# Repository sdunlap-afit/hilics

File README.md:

<div>
  
</div>
<br clear="all" />
<br>

<div align="center">

</div>

# HILICS - Hardware-in-the-loop industrial control system training platform

The Center for Cyberspace Research (CCR) has conducted extensive research in Industrial Control System (ICS) security. ICS architectures utilize a variety of proprietary hardware and software configurations to control and monitor industrial processes and safety systems. Defenders must be familiar with the functionality, requirements and limitations of control systems in order to successfully defend them from cyber-attacks. Hands-on training and experience is crucial for defenders who must be able to interact safely with a given control system. Without this experience, defenders could mistakenly take actions that cause more harm to the system than a basic cyber-attack.  

Given the physical nature of ICS architectures, training platforms can be difficult and costly to develop. To address this, the CCR has developed HILICS - a unique hardware-in-the-loop ICS platform designed to support training, education and research. HILICS utilizes a MicroLogix 1100 Programmable Logic Controller (PLC) to introduce students to PLC operating basics and the associated programming languages. This PLC is a low-cost commercial product that provides a representative set of features to give students exposure to control system functionality. The HILICS platform is a custom hardware-in-the-loop system that enables trainers to incorporate multiple physical process simulations and expose students to a range of control system applications. The platform is designed to be flexible and scalable, allowing for varying class sizes and supporting various control system applications.  

# How it works

HILICS is a hardware-in-the-loop training system. A Raspberry Pi provides simulations of physical processes such as fluid tanks or garage doors. Each simulation is made up of sensors, actuators and physical components such as pipes or tanks. **The Raspberry Pi does not have any network connection to the PLC.**

We will use the tank simulation as an example.

## Sensors

The Raspberry Pi simulation determines the current state of the process and calculates the values of the simulated sensors. The sensor values are sent to the PLC via the interface PCB. The PLC receives these values as voltages using it's digital and analog inputs. The PLC's ladder logic program determines how the PLC responds to the sensor values.

For the tank, there are two analog sensors and three digital sensors.

* Analog Sensors:
	* Inflow differential pressure transmitter.
	* Fluid level differential pressure transmitter.
* Digital Sensors:
	* Low level float
	* High level float
	* High-High level float
* Other:
	* This simulation was designed to work without the presence of an HMI. Typically, an HMI would be used to select set points for the process.
	* The Inflow SP button panel uses two of the PLC's digital inputs to send the desired inflow rate to the PLC.
	* The Level SP button panel uses two of the PLC's digital inputs to send the desired fluid level of the tank to the PLC.

## Actuators

The PLC reads the values of the sensors, compares them to the desired values and then adjusts it's outputs (as voltages) to control the actuators. The Raspberry Pi receives these values via the interface PCB and adjusts the simulation appropriately. 

For the tank, there are two analog actuators.

* Pump - the speed of the pump is used to calculate the current inflow rate into the tank.
* Valve - the position of the valve is used to calculate the outflow rate draining from the tank.

While the tank only has analog actuators, an example of a digital actuator is an indicator light controlled by the PLC's digital outputs.

Find further details about this simulation [here.](../labs/L3_Tank_Control.md)

# What's Included

## Documentation

The [docs](./docs) folder contains various documents including a bill-of-materials, hardware assembly and computer setup instructions.

## Source code

This repository contains all of the Python [source code](./src) you need to get started. The [apps](./src/apps) folder contains the following Applications:

* [IO_Test.py](./src/apps/IO_Test.py) - Basic app to test the functionality of the HILICS kit.
* [Door.py](./src/apps/Door.py) - Garage door simulation.
* [Fluid_Tank.py](./src/apps/Fluid_Tank.py) - Fluid tank with two control loops.
* [Blank_App.py](./src/apps/Blank_App.py) - A template to help you get started writing your own app.
* [Test_App.py](./src/apps/Test_App.py) - An app you can enable and edit to test your display elements during development.

## Hardware

The [hardware](./hardware) folder contains the design files and stl files you need to 3D print the frame for HILICS.

The [eagle](./hardware/eagle) folder contains all of the PCB design files and BOM.

## Labs

HILICS was designed for use in cyber security education, but the labs released here only cover basic PLC operations. Future labs may cover cyber concepts. 

The [labs](./labs) folder contains three basic labs to get started.

* [Lab 1](./labs/L1_Setup.md) - Get connected to your PLC and start programming in ladder logic.
* [Lab 2](./labs/L2_Door_Control.md) - Write a ladder logic program to control a garage door simulation.
* [Lab 3](./labs/L3_Tank_Control.md) - Learn the basics of PID control and PID tuning.

# Getting Started

## [Read the docs](./docs/README.md)

## [Try the labs](./labs/README.md)

## Contribute

This repository is not currently maintained and we will not be accepting any pull requests. If we develop any additional capabilities, we will release them here. If enough interest is shown, we might begin actively maintaining the repository. 

If you would like to contribute, look at the existing forks, or feel free to start your own.

# Disclaimer

Note that the views expressed in this project are those of
the authors and do not reflect the official policy or position of
the U.S. Air Force, U.S. Department of Defense or the U.S.
Government.

Approved for public release, 24 Sep 2019, Case #88ABW-2019-4607.

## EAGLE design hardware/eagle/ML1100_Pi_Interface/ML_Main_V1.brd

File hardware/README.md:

<div>
  
</div>
<br clear="all" />
<br>

# Custom Hardware

## [Interface PCBs](./eagle/ML1100_Pi_Interface)

For each HILICS kit, you will need one each of the five [Interface PCBs](./eagle/ML1100_Pi_Interface). The bill of materials is in the folder with the PCBs. The BOM is for Digikey but provides specifications if you want to source components from a different supplier.

**You will also need 40-pin male headers for the Raspberry Pi ribbon cable to connect to the main PCB. These are cheaper on Amazon.**

If you plan to solder these by hand, make sure you are competent with surface mount soldering techniques. It may also be helpful to modify the main PCB design to use resistor arrays instead of individual resistors. Similar modifications can help reduce the amount of soldering required.

## [3D printing](./cad/stl_files)

The frame was designed in sections so that the largest part (135mm x 210mm) would still fit on a smaller 3D printer. 
We printed all of our components using black PLA without any supports. 
The amount of time and filament it will take depends heavily on your 3D printer settings.

 Our settings:

* 0.4mm layer height (0.2mm first layer height)
* 0.6mm nozzle
* 2 perimeters
* 3 bottom layers
* 3 top layers
* 20% infill

You will need to 3D print the following stl files (quantities listed):

* 1x - PLC Frame - 1x_HILICS_PLC_Frm.stl
* 2x - Raspberry PI Frame - 2x_HILICS_Pi_Frm.stl
* 2x - PCB legs - 2x_PCB_Leg.stl
* 3x - Extension Blocks - 3x_HILICS_ExtBlck.stl
* 1x - Choice of power box:
	* Multi-color: HILICS_Power_Color_* are individual stl files for multi-extruder/multi-color printers.
	* Single-color: HILICS_Power_single_ext.stl is for single extruder/color printers.

If you need to make modifications to the design, the Fusion 360 design files are [here.](./cad/Fusion360)

## [Nameplates](./cad/Nameplates)

You may also want to print [nameplates](./cad/Nameplates) for the front of your Pelican cases to uniquely identify each HILICS kit. We printed ours in white PLA

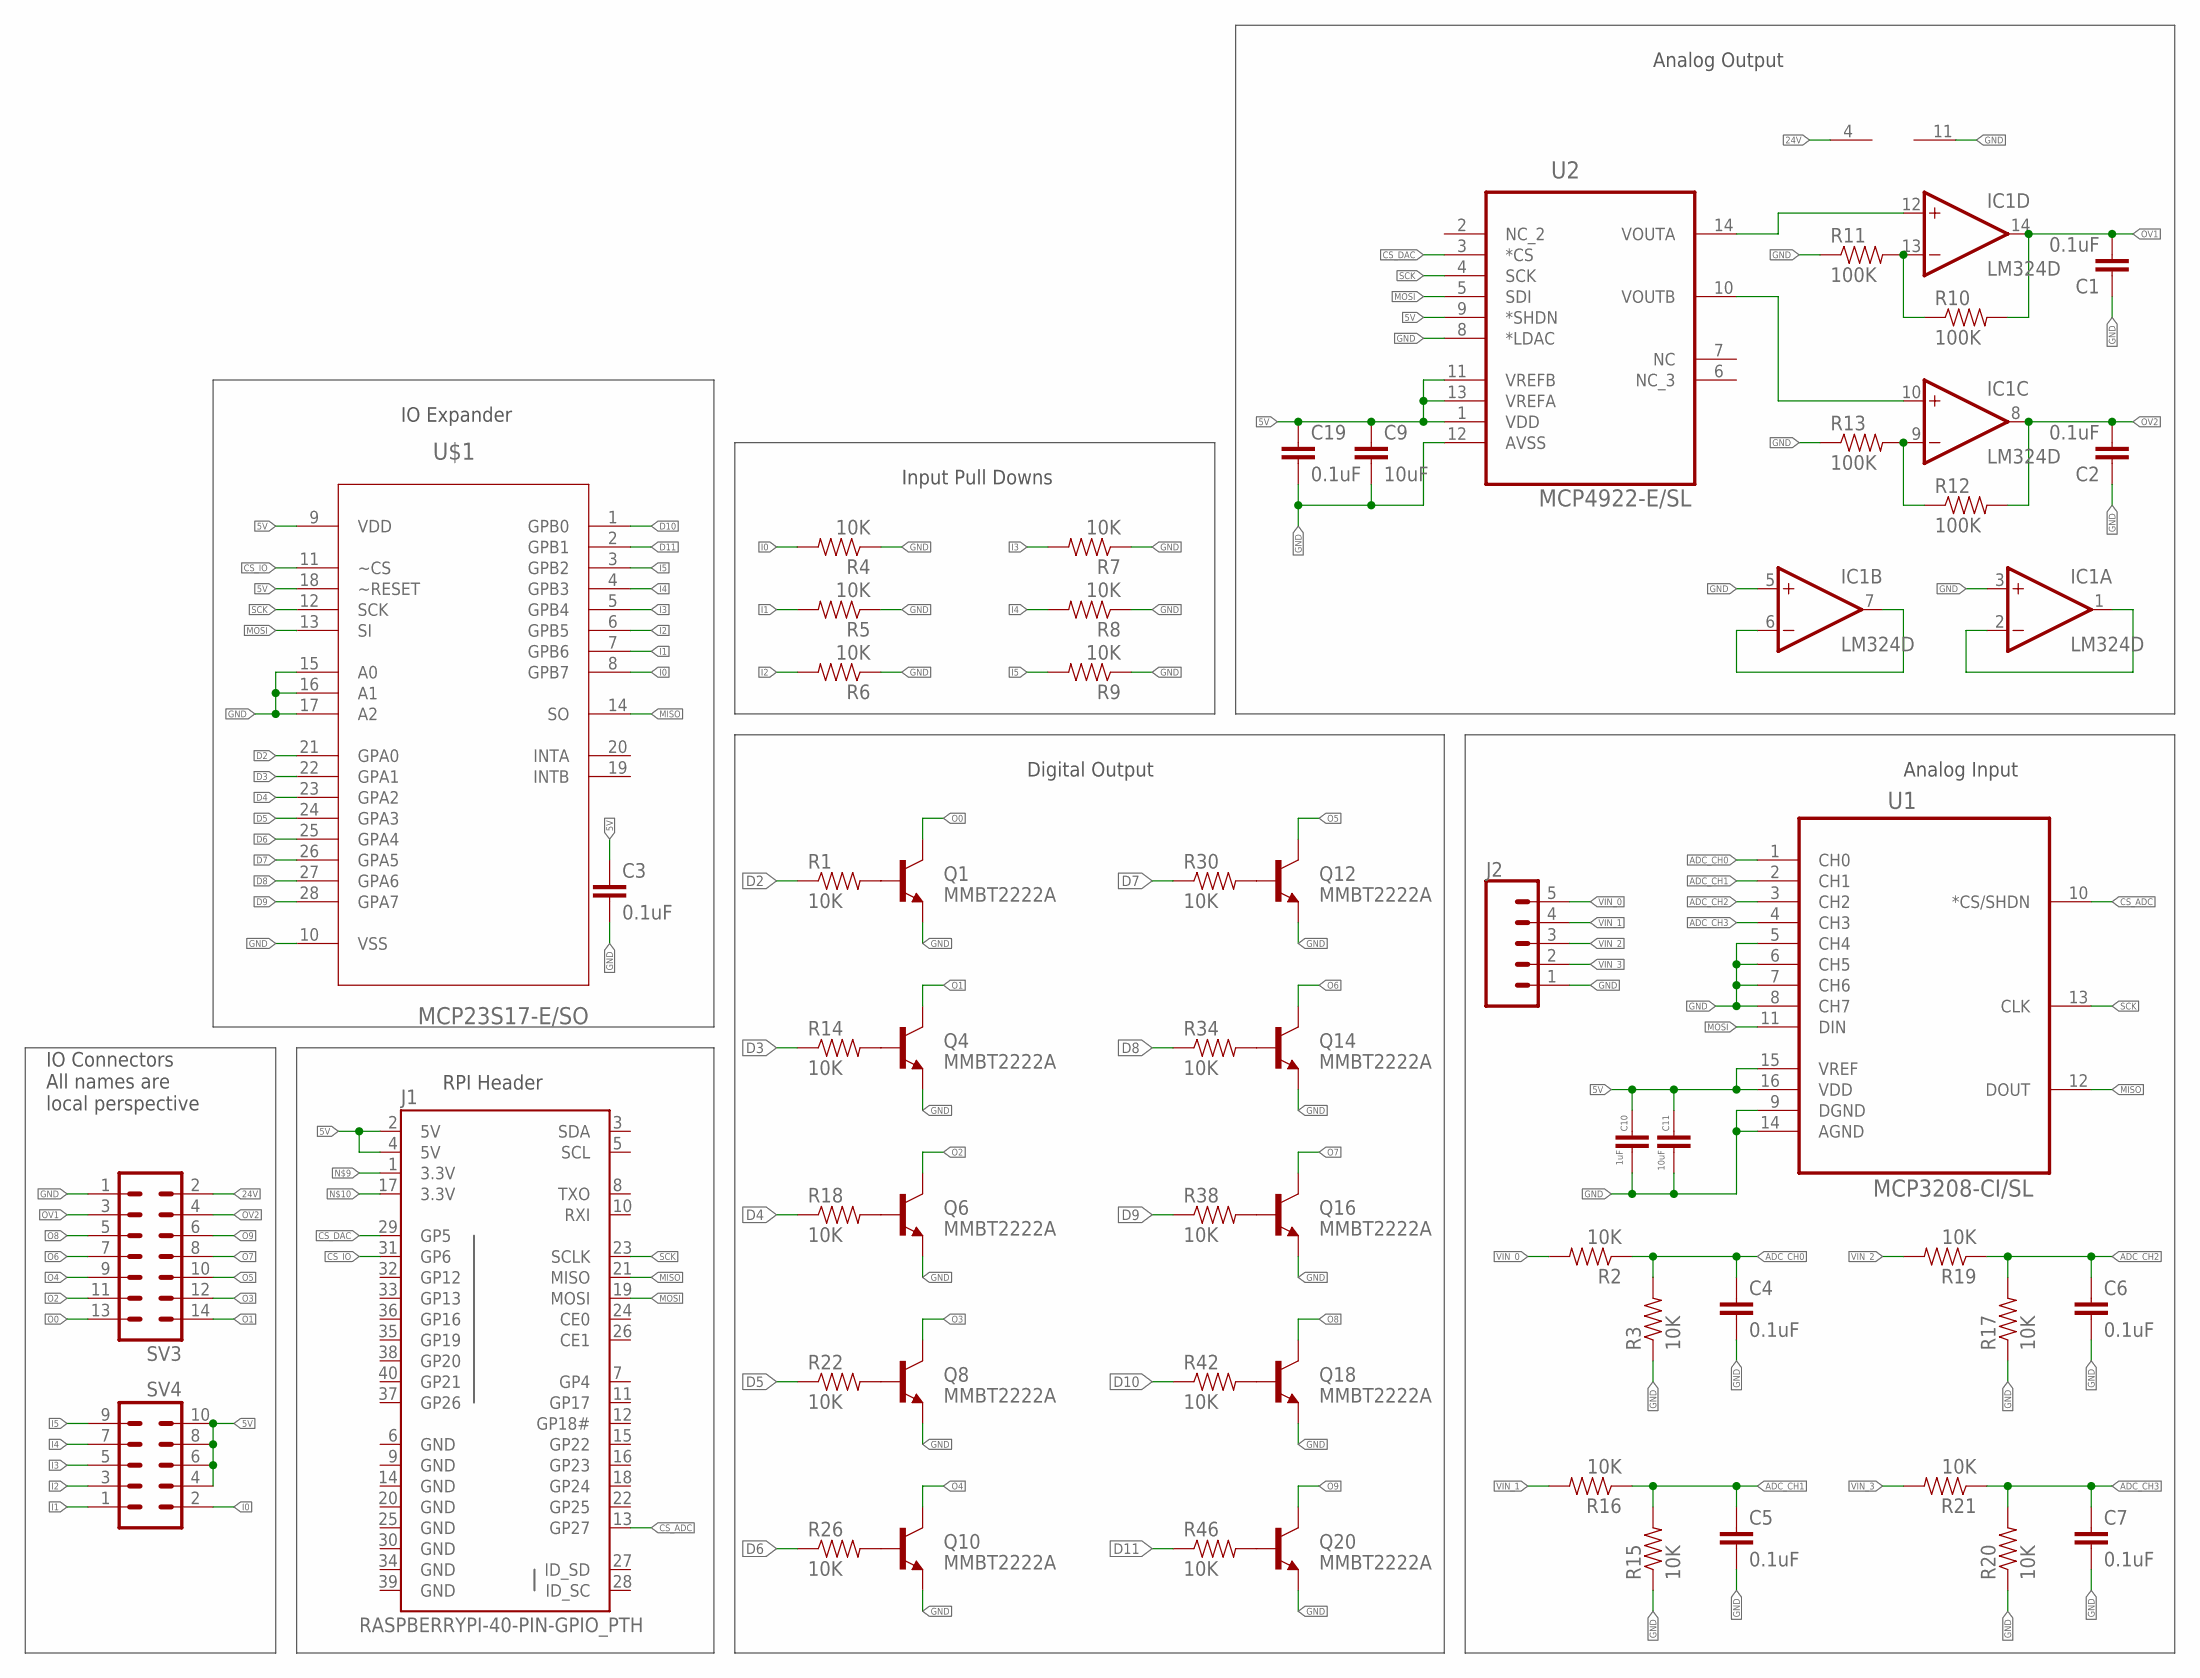
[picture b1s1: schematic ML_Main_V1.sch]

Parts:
C1, C2, C3, C4, C5, C6, C7, C19: 0.1uF; 0603-CAP
C9, C11: 10uF; 0603-CAP
C10: 1uF; 0603-CAP
IC1: LM324D; SO14
J1: RASPBERRYPI-40-PIN-GPIO_PTH; 2X20_SHROUDED
J2: CONN_05SCREW; SCREWTERMINAL-3.5MM-5
Q1, Q4, Q6, Q8, Q10, Q12, Q14, Q16, Q18, Q20: MMBT2222A; SOT23-3
R1, R2, R3, R4, R5, R6, R7, R8, R9, R14, R15, R16, R17, R18, R19, R20, R21, R22, R26, R30, R34, R38, R42, R46: 10K; 0603-RES
R10, R11, R12, R13: 100K; 0603-RES
SV3: MA07-2W
SV4: MA05-2
U1: MCP3208-CI/SL; SOIC127P600X175-16N
U2: MCP4922-E/SL; SOIC127P600X175-14N
U$1: MCP23S17-E/SO; SOIC127P030X265-28N

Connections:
5V: C3.1, C9.1, C10.1, C11.1, C19.1, J1.2 (5V), J1.4 (5V), SV4.4, SV4.6, SV4.8, SV4.10, U1.15 (VREF), U1.16 (VDD), U2.1 (VDD), U2.9 (*SHDN), U2.11 (VREFB), U2.13 (VREFA), U$1.9 (VDD), U$1.18 (~RESET)
24V: IC1.4 (V+), SV3.2
ADC_CH0: C4.1, R2.1, R3.2, U1.1 (CH0)
ADC_CH1: C5.1, R15.2, R16.1, U1.2 (CH1)
ADC_CH2: C6.1, R17.2, R19.1, U1.3 (CH2)
ADC_CH3: C7.1, R20.2, R21.1, U1.4 (CH3)
CS_ADC: J1.13 (GP27), U1.10 (*CS/SHDN)
CS_DAC: J1.29 (GP5), U2.3 (*CS)
CS_IO: J1.31 (GP6), U$1.11 (~CS)
D2: R1.1, U$1.21 (GPA0)
D3: R14.1, U$1.22 (GPA1)
D4: R18.1, U$1.23 (GPA2)
D5: R22.1, U$1.24 (GPA3)
D6: R26.1, U$1.25 (GPA4)
D7: R30.1, U$1.26 (GPA5)
D8: R34.1, U$1.27 (GPA6)
D9: R38.1, U$1.28 (GPA7)
D10: R42.1, U$1.1 (GPB0)
D11: R46.1, U$1.2 (GPB1)
GND: C1.1, C2.1, C3.2, C4.2, C5.2, C6.2, C7.2, C9.2, C10.2, C11.2, C19.2, IC1.3 (+IN), IC1.5 (+IN), IC1.11 (V-), J1.6 (GND), J1.9 (GND), J1.14 (GND), J1.20 (GND), J1.25 (GND), J1.30 (GND), J1.34 (GND), J1.39 (GND), J2.1, Q1.2 (E), Q4.2 (E), Q6.2 (E), Q8.2 (E), Q10.2 (E), Q12.2 (E), Q14.2 (E), Q16.2 (E), Q18.2 (E), Q20.2 (E), R3.1, R4.1, R5.1, R6.1, R7.1, R8.1, R9.1, R11.1, R13.1, R15.1, R17.1, R20.1, SV3.1, U1.5 (CH4), U1.6 (CH5), U1.7 (CH6), U1.8 (CH7), U1.9 (DGND), U1.14 (AGND), U2.8 (*LDAC), U2.12 (AVSS), U$1.10 (VSS), U$1.15 (A0), U$1.16 (A1), U$1.17 (A2)
I0: R4.2, SV4.2, U$1.8 (GPB7)
I1: R5.2, SV4.1, U$1.7 (GPB6)
I2: R6.2, SV4.3, U$1.6 (GPB5)
I3: R7.2, SV4.5, U$1.5 (GPB4)
I4: R8.2, SV4.7, U$1.4 (GPB3)
I5: R9.2, SV4.9, U$1.3 (GPB2)
MISO: J1.21 (MISO), U1.12 (DOUT), U$1.14 (SO)
MOSI: J1.19 (MOSI), U1.11 (DIN), U2.5 (SDI), U$1.13 (SI)
unnamed: IC1.13 (-IN), R10.1, R11.2
unnamed: Q1.1 (B), R1.2
unnamed: IC1.10 (+IN), U2.10 (VOUTB)
unnamed: IC1.12 (+IN), U2.14 (VOUTA)
unnamed: IC1.9 (-IN), R12.1, R13.2
unnamed: IC1.1 (OUT), IC1.2 (-IN)
unnamed: IC1.6 (-IN), IC1.7 (OUT)
unnamed: Q4.1 (B), R14.2
unnamed: Q6.1 (B), R18.2
unnamed: Q8.1 (B), R22.2
unnamed: Q10.1 (B), R26.2
unnamed: Q12.1 (B), R30.2
unnamed: Q14.1 (B), R34.2
unnamed: Q16.1 (B), R38.2
unnamed: Q18.1 (B), R42.2
unnamed: Q20.1 (B), R46.2
O0: Q1.3 (C), SV3.13
O1: Q4.3 (C), SV3.14
O2: Q6.3 (C), SV3.11
O3: Q8.3 (C), SV3.12
O4: Q10.3 (C), SV3.9
O5: Q12.3 (C), SV3.10
O6: Q14.3 (C), SV3.7
O7: Q16.3 (C), SV3.8
O8: Q18.3 (C), SV3.5
O9: Q20.3 (C), SV3.6
OV1: C1.2, IC1.14 (OUT), R10.2, SV3.3
OV2: C2.2, IC1.8 (OUT), R12.2, SV3.4
SCK: J1.23 (SCLK), U1.13 (CLK), U2.4 (SCK), U$1.12 (SCK)
VIN_0: J2.5, R2.2
VIN_1: J2.4, R16.2
VIN_2: J2.3, R19.2
VIN_3: J2.2, R21.2

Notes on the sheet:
IO Connectors All names are local perspective
Digital Output
Input Pull Downs
Analog Output
RPI Header
IO Expander
Analog Input

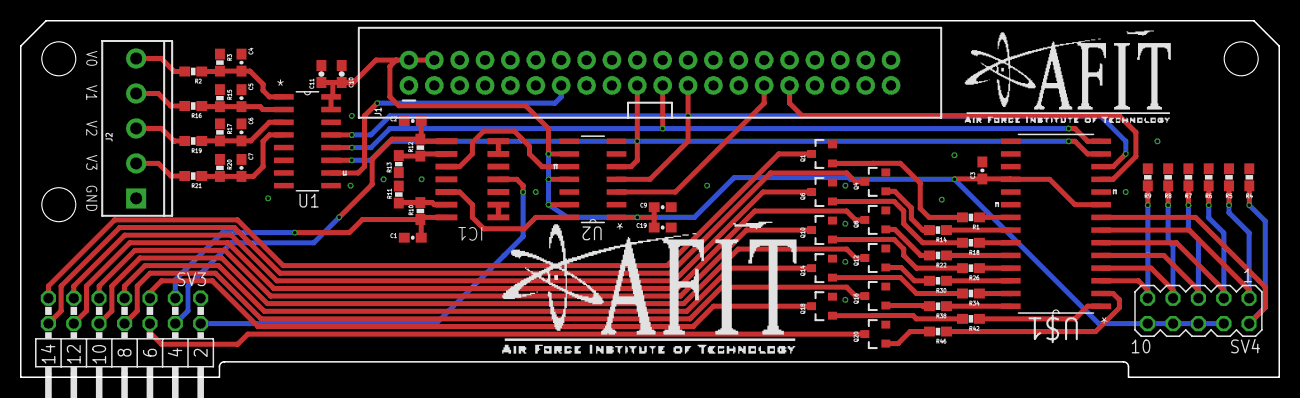
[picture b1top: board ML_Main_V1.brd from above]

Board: 2 copper layers, 126.0 x 35.7 mm, 57 parts (0 on the bottom side), 61 nets.

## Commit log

2021-01-05 Updated to match newest rpi OS version
2021-03-29 Bump pygments from 2.3.1 to 2.7.4 in /hardware/cad/Nameplates
    Bumps [pygments](https://github.com/pygments/pygments) from 2.3.1 to 2.7.4.
    - [Release notes](https://github.com/pygments/pygments/releases)
    - [Changelog](https://github.com/pygments/pygments/blob/master/CHANGES)
    - [Commits](https://github.com/pygments/pygments/compare/2.3.1...2.7.4)
2021-06-17 Fixed bug that broke pump and valve in tank sim
2021-07-06 Changed colors to match github dark mode
2021-07-06 Added background for github dark mode
2021-07-15 Fixed a threading bug
2021-11-09 Added standard python gitignore
2021-11-09 Template setup for blank sim
2021-11-19 Added base ServerRoom app
2021-11-19 ignore vscode folder
2021-11-19 Comm class for network sensors/actuators
2021-12-17 Refactored SimIO and start linking up sensors/actuators
2022-01-07 Added graphic for server rack
2022-01-14 Added servers and zone classes with basic numbers
2022-01-21 Bump ipython from 7.2.0 to 7.16.3 in /hardware/cad/Nameplates
    Bumps [ipython](https://github.com/ipython/ipython) from 7.2.0 to 7.16.3.
    - [Release notes](https://github.com/ipython/ipython/releases)
    - [Commits](https://github.com/ipython/ipython/compare/7.2.0...7.16.3)
    ---
    updated-dependencies:
    - dependency-name: ipython
2022-01-21 Basic simulation working
2023-05-03 Updated install scripts for tinker board and vnc

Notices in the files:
parts and their libraries:
SparkFun-DiscreteSemi: Licensing: Creative Commons ShareAlike 4.0 International - https://creativecommons.org/licenses/by-sa/4.0
